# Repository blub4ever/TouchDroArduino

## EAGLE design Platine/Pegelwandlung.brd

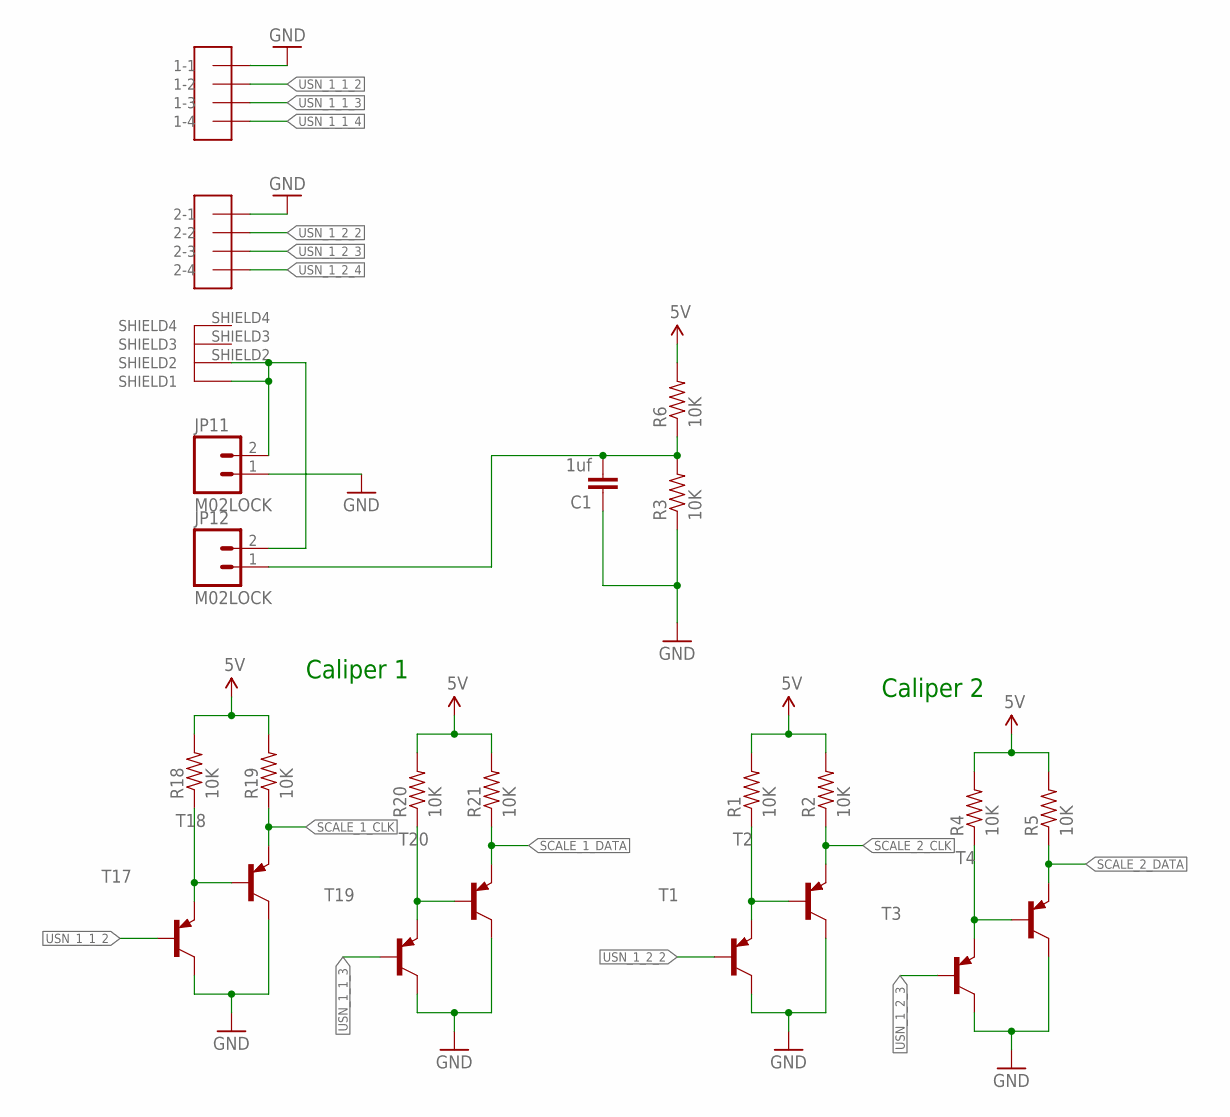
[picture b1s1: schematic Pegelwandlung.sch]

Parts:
C1: 1uf; 0805
JP11, JP12: M02LOCK; 1X02_LOCK
R1, R2, R3, R4, R5, R6, R18, R19, R20, R21: 10K; 0603-RES
T1, T2, T3, T4, T17, T18, T19, T20: -PNP-SOT23-BCE; SOT23-BCE
U$7: USB-A-2

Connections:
1.5V: C1.2, JP12.1, R3.2, R6.1
5V: R1.2, R2.2, R4.2, R5.2, R6.2, R18.2, R19.2, R20.2, R21.2
GND: C1.1, JP11.1, R3.1, T1.C, T2.C, T3.C, T4.C, T17.C, T18.C, T19.C, T20.C, U$7.1-1, U$7.2-1
unnamed: R1.1, T1.E, T2.B
unnamed: JP11.2, JP12.2, U$7.SHIELD1, U$7.SHIELD2
unnamed: R18.1, T17.E, T18.B
unnamed: R4.1, T3.E, T4.B
unnamed: R20.1, T19.E, T20.B
SCALE_1_CLK: R19.1, T18.E
SCALE_1_DATA: R21.1, T20.E
SCALE_2_CLK: R2.1, T2.E
SCALE_2_DATA: R5.1, T4.E
USN_1_1_2: T17.B, U$7.1-2
USN_1_1_3: T19.B, U$7.1-3
USN_1_1_4: U$7.1-4
USN_1_2_2: T1.B, U$7.2-2
USN_1_2_3: T3.B, U$7.2-3
USN_1_2_4: U$7.2-4

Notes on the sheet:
Caliper 2
Caliper 1

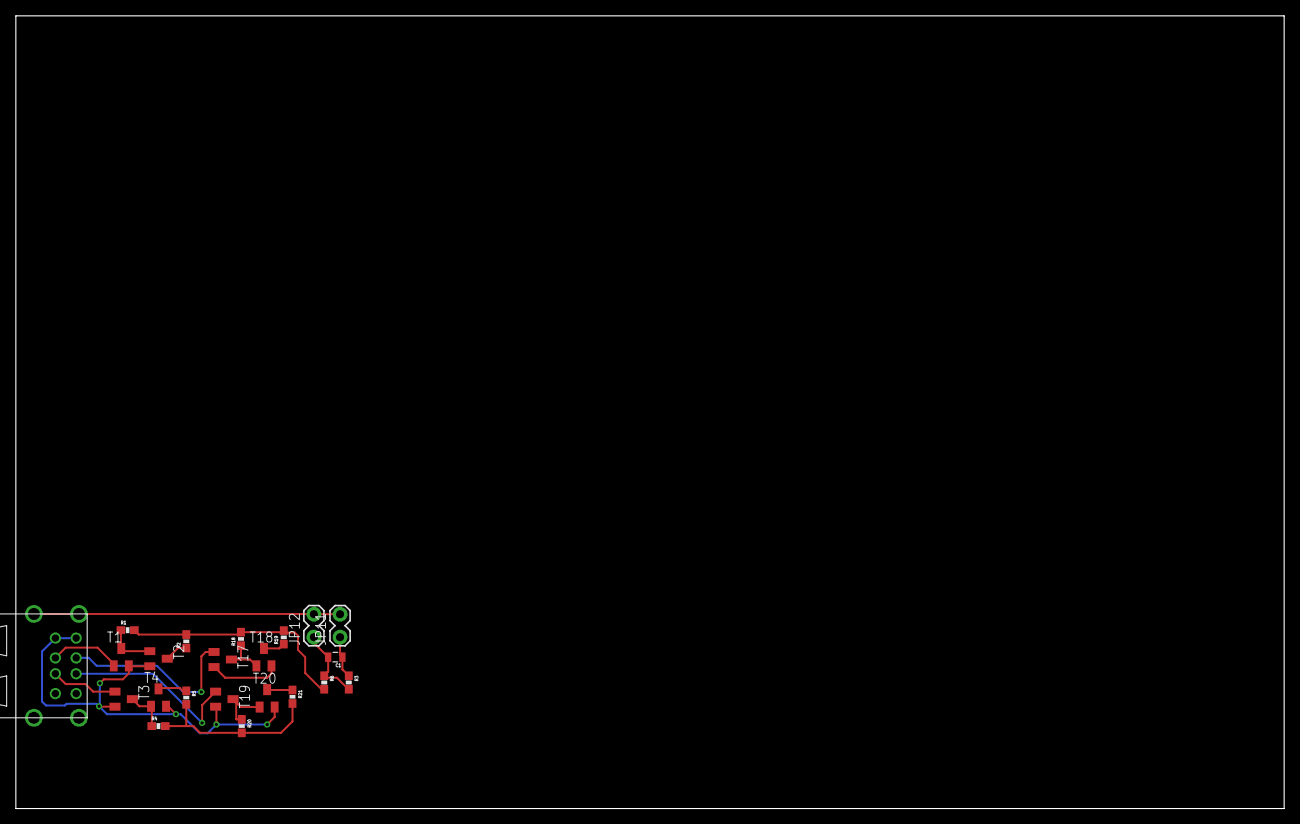
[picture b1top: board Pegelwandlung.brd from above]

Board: 2 copper layers, 160.0 x 100.0 mm, 22 parts (0 on the bottom side), 16 nets.

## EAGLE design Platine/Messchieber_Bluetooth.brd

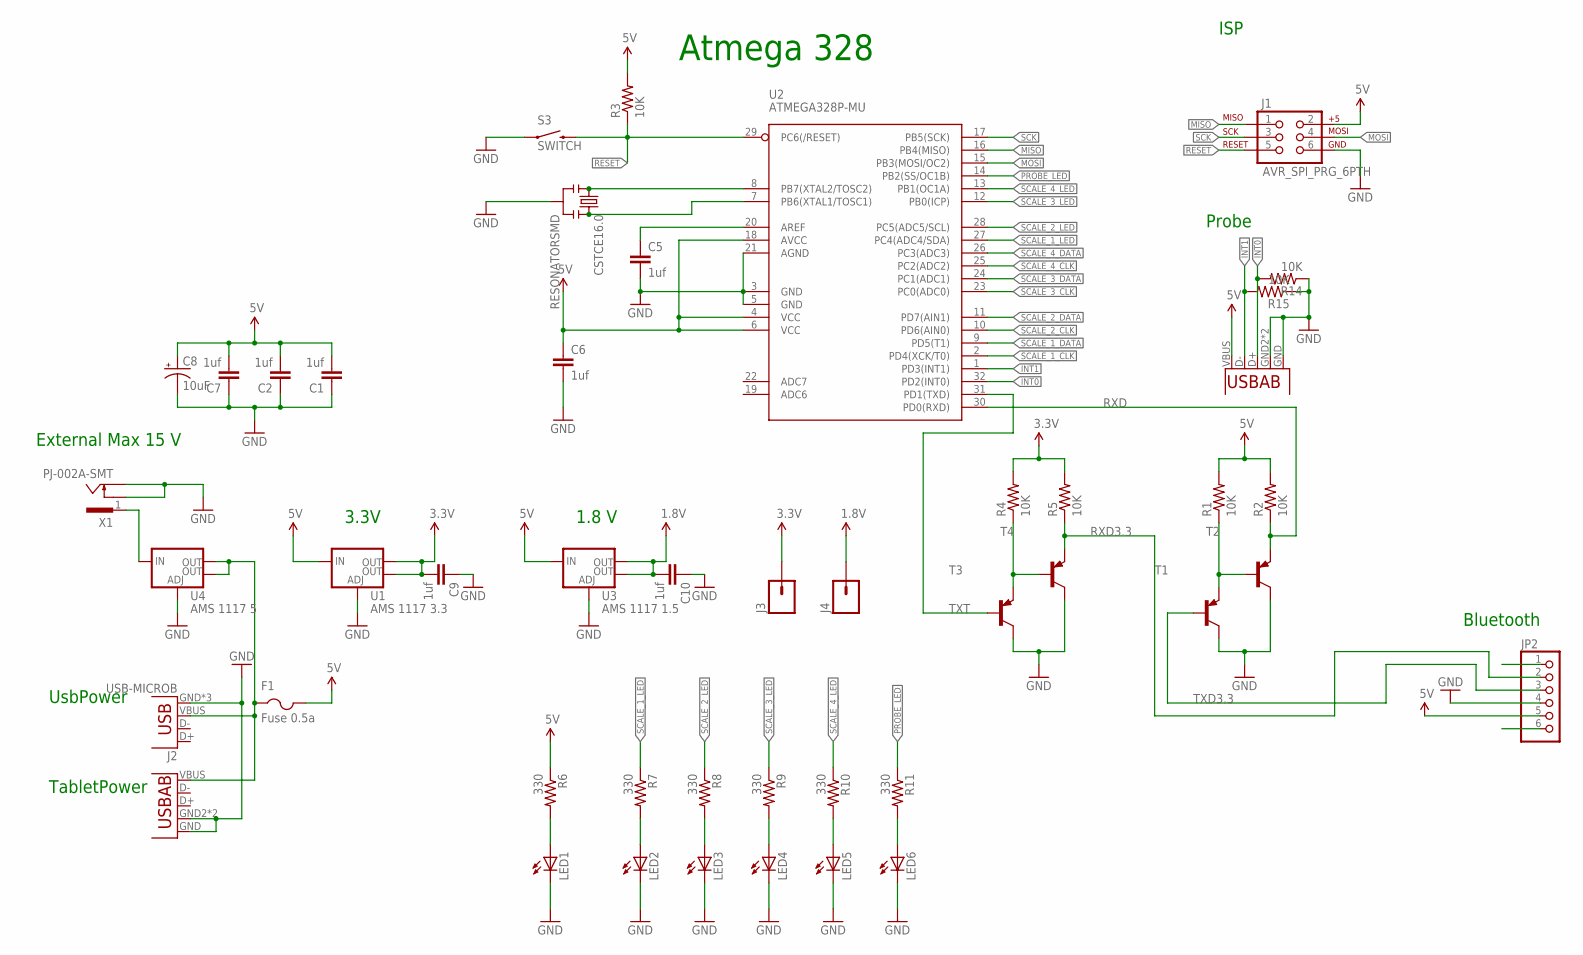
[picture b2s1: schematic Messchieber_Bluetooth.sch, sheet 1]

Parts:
C1, C2, C5, C6, C7, C9, C10: 1uf; 0805
C8: 10uF; EIA3528
CSTCE16.0: RESONATORSMD; RESONATOR-SMD
F1: Fuse 0.5a; 1812
J1: AVR_SPI_PRG_6PTH; 2X3
J2: USB-MICROB
J3, J4: M01PTH; 1X01
JP2: PINHD-1X6; 1X06
LED1, LED2, LED3, LED4, LED5, LED6: LEDSML0805; SML0805
R1, R2, R3, R4, R5, R14, R15: 10K; 0603-RES
R6, R7, R8, R9, R10, R11: 330; 0603
S3: SWITCH; TACTILE-SWITCH-1101NE
T1, T2, T3, T4: -PNP-SOT23-BCE; SOT23-BCE
U1: AMS 1117 3.3; SOT223
U2: ATMEGA328P-MU; TQFP32-08@1
U3: AMS 1117 1.5; SOT223
U4: AMS 1117 5; SOT223
U$1, U$4: USB-A
X1: PJ-002A-SMT; CUI_PJ-002B-SMT

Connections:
1.8V: C10.2, J4.1, U3.2 (OUT), U3.4 (OUT); also elsewhere on the board
3.3V: C9.2, J3.1, R4.2, R5.2, U1.2 (OUT), U1.4 (OUT)
5V: C1.2, C2.2, C6.1, C7.2, C8.A (+), F1.2, J1.2, JP2.5, R1.2, R2.2, R3.2, R6.1, U1.3 (IN), U2.4 (VCC), U2.6 (VCC), U2.18 (AVCC), U3.3 (IN), U$1.VBUS; also elsewhere on the board
GND: C1.1, C2.1, C5.2, C6.2, C7.1, C8.C (-), C9.1, C10.1, CSTCE16.0.2, J1.6, J2.GND, J2.MT1 (GND), J2.MT2 (GND), JP2.4, LED1.C, LED2.C, LED3.C, LED4.C, LED5.C, LED6.C, R14.1, R15.1, S3.P$1 (1), T1.C, T2.C, T3.C, T4.C, U1.1 (ADJ), U2.3 (GND), U2.5 (GND), U2.21 (AGND), U3.1 (ADJ), U4.1 (ADJ), U$1.GND, U$1.GND2 (USBID), U$1.GND3 (USBID), U$4.GND, U$4.GND2 (USBID), U$4.GND3 (USBID), X1.3, X1.4; also elsewhere on the board
INT0: R14.2, U2.32 (PD2(INT0)), U$1.D+
INT1: R15.2, U2.1 (PD3(INT1)), U$1.D-
MISO: J1.1, U2.16 (PB4(MISO))
MOSI: J1.4, U2.15 (PB3(MOSI/OC2))
unnamed: C5.1, U2.20 (AREF)
unnamed: R1.1, T1.E, T2.B
unnamed: R4.1, T3.E, T4.B
unnamed: LED2.A, R7.2
unnamed: CSTCE16.0.1, U2.8 (PB7(XTAL2/TOSC2))
unnamed: F1.1, J2.VBUS, U4.2 (OUT), U4.4 (OUT), U$4.VBUS
unnamed: U4.3 (IN), X1.1
unnamed: LED3.A, R8.2
unnamed: LED1.A, R6.2
unnamed: LED4.A, R9.2
unnamed: LED5.A, R10.2
unnamed: LED6.A, R11.2
unnamed: CSTCE16.0.3, U2.7 (PB6(XTAL1/TOSC1))
PROBE_LED: R11.1, U2.14 (PB2(SS/OC1B))
RESET: J1.5, R3.1, S3.P$2 (2), U2.29 (PC6(/RESET))
RXD: R2.1, T2.E, U2.30 (PD0(RXD))
RXD3.3: JP2.2, R5.1, T4.E
SCALE_1_CLK: U2.2 (PD4(XCK/T0)); also elsewhere on the board
SCALE_1_DATA: U2.9 (PD5(T1)); also elsewhere on the board
SCALE_1_LED: R7.1, U2.27 (PC4(ADC4/SDA))
SCALE_2_CLK: U2.10 (PD6(AIN0)); also elsewhere on the board
SCALE_2_DATA: U2.11 (PD7(AIN1)); also elsewhere on the board
SCALE_2_LED: R8.1, U2.28 (PC5(ADC5/SCL))
SCALE_3_CLK: U2.23 (PC0(ADC0)); also elsewhere on the board
SCALE_3_DATA: U2.24 (PC1(ADC1)); also elsewhere on the board
SCALE_3_LED: R9.1, U2.12 (PB0(ICP))
SCALE_4_CLK: U2.25 (PC2(ADC2)); also elsewhere on the board
SCALE_4_DATA: U2.26 (PC3(ADC3)); also elsewhere on the board
SCALE_4_LED: R10.1, U2.13 (PB1(OC1A))
SCK: J1.3, U2.17 (PB5(SCK))
TXD3.3: JP2.3, T1.B
TXT: T3.B, U2.31 (PD1(TXD))

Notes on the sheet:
Atmega 328
Bluetooth
Probe
ISP
UsbPower
TabletPower
External Max 15 V
3.3V
1.8 V

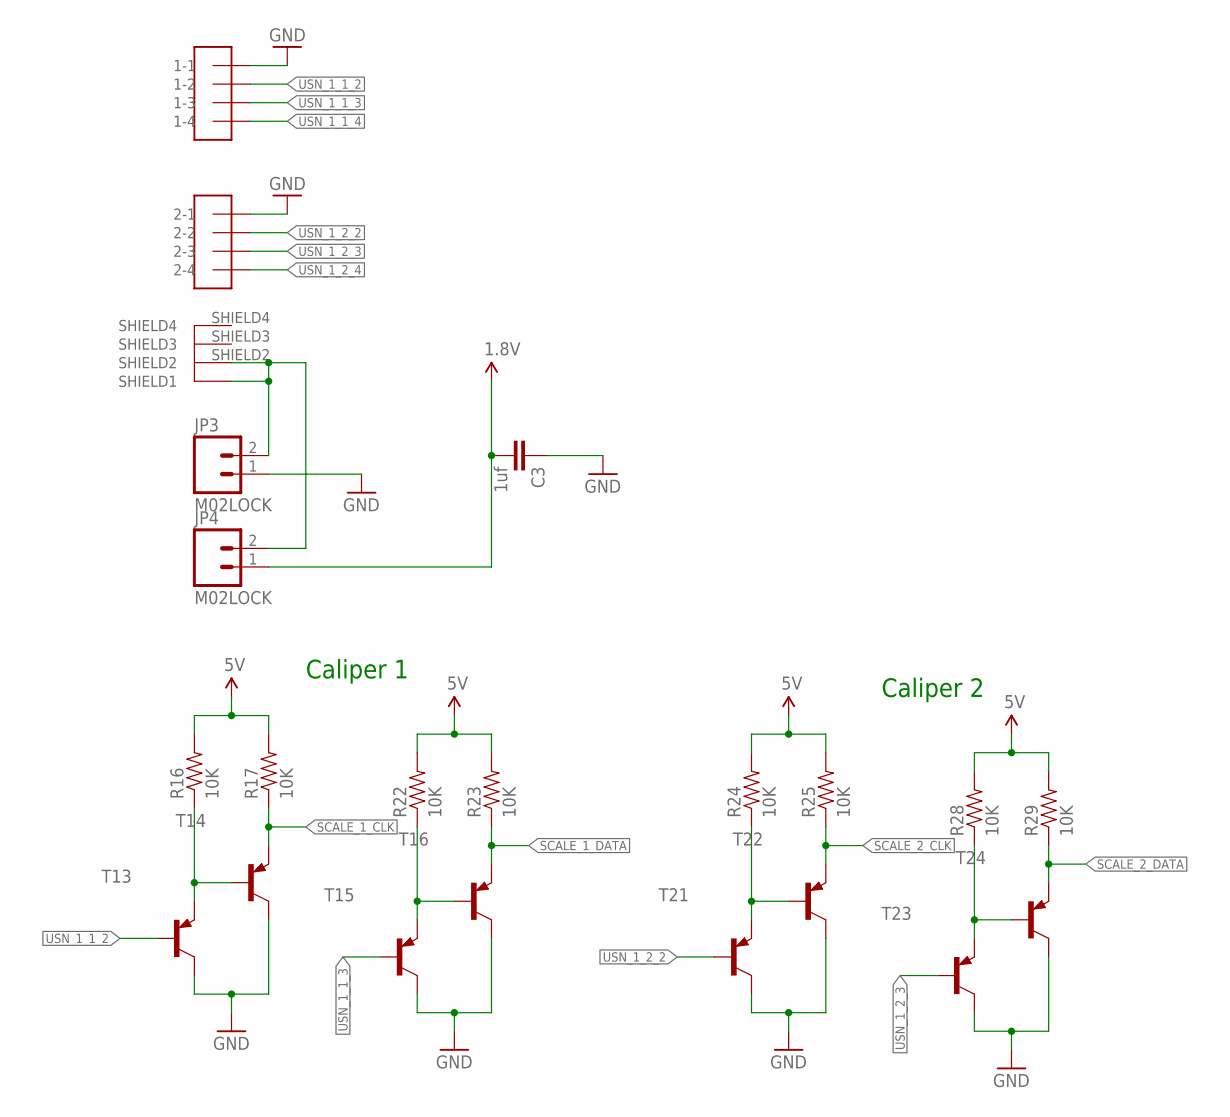
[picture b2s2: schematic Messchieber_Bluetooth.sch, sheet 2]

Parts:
C3: 1uf; 0805
JP3, JP4: M02LOCK; 1X02_LOCK
R16, R17, R22, R23, R24, R25, R28, R29: 10K; 0603-RES
T13, T14, T15, T16, T21, T22, T23, T24: -PNP-SOT23-BCE; SOT23-BCE
U$2: USB-A-2

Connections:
1.8V: C3.2, JP4.1; also elsewhere on the board
5V: R16.2, R17.2, R22.2, R23.2, R24.2, R25.2, R28.2, R29.2; also elsewhere on the board
GND: C3.1, JP3.1, T13.C, T14.C, T15.C, T16.C, T21.C, T22.C, T23.C, T24.C, U$2.1-1, U$2.2-1; also elsewhere on the board
unnamed: JP3.2, JP4.2, U$2.SHIELD1, U$2.SHIELD2
unnamed: R16.1, T13.E, T14.B
unnamed: R22.1, T15.E, T16.B
unnamed: R24.1, T21.E, T22.B
unnamed: R28.1, T23.E, T24.B
SCALE_1_CLK: R17.1, T14.E; also elsewhere on the board
SCALE_1_DATA: R23.1, T16.E; also elsewhere on the board
SCALE_2_CLK: R25.1, T22.E; also elsewhere on the board
SCALE_2_DATA: R29.1, T24.E; also elsewhere on the board
USN_1_1_2: T13.B, U$2.1-2
USN_1_1_3: T15.B, U$2.1-3
USN_1_1_4: U$2.1-4
USN_1_2_2: T21.B, U$2.2-2
USN_1_2_3: T23.B, U$2.2-3
USN_1_2_4: U$2.2-4

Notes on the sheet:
Caliper 2
Caliper 1

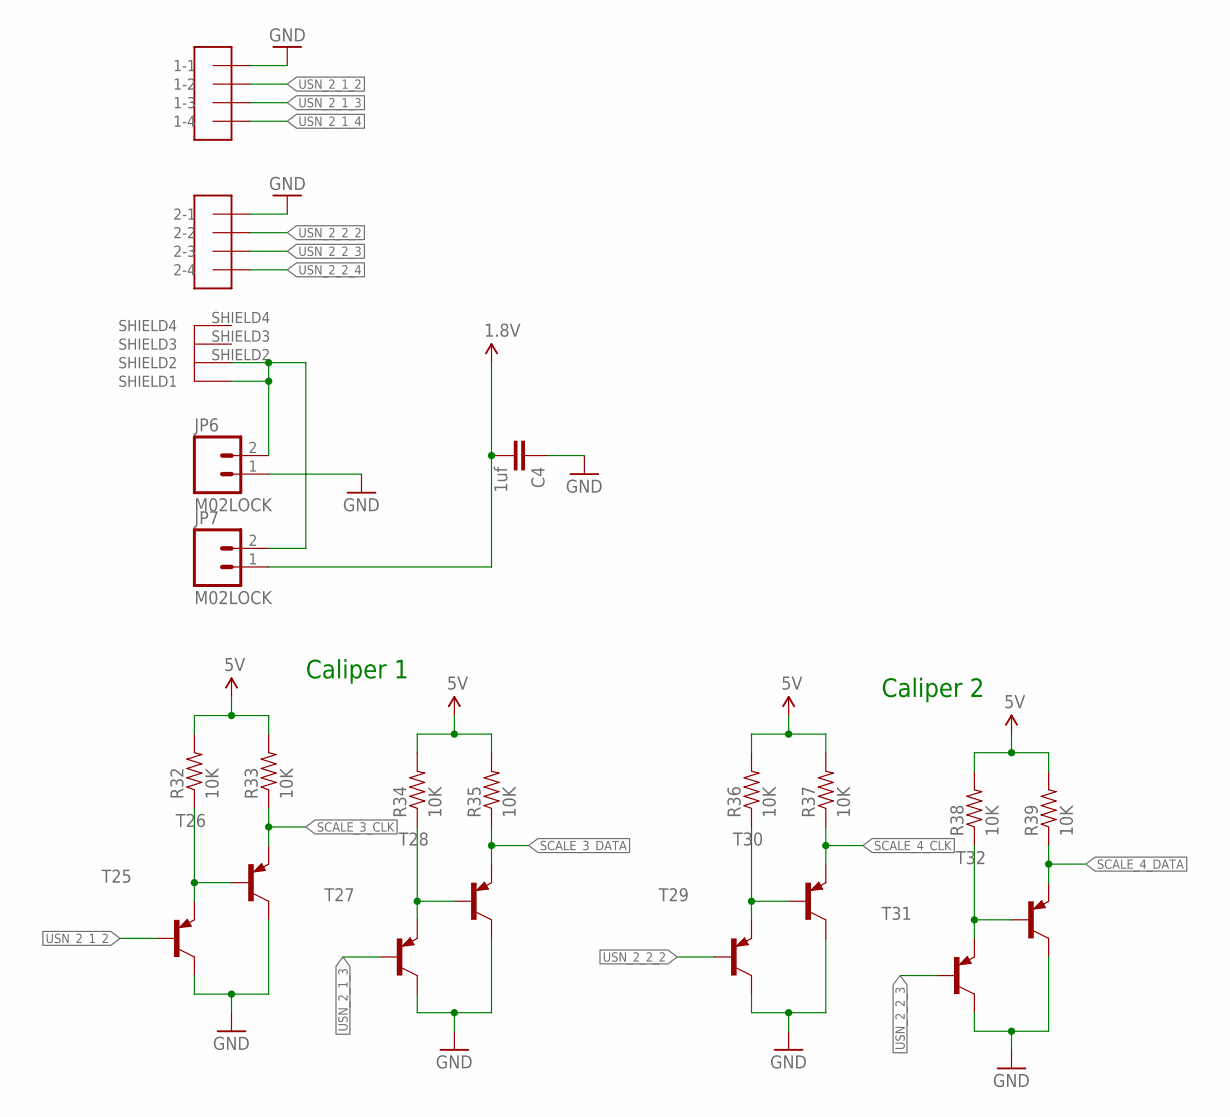
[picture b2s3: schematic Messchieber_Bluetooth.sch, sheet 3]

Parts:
C4: 1uf; 0805
JP6, JP7: M02LOCK; 1X02_LOCK
R32, R33, R34, R35, R36, R37, R38, R39: 10K; 0603-RES
T25, T26, T27, T28, T29, T30, T31, T32: -PNP-SOT23-BCE; SOT23-BCE
U$3: USB-A-2

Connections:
1.8V: C4.2, JP7.1; also elsewhere on the board
5V: R32.2, R33.2, R34.2, R35.2, R36.2, R37.2, R38.2, R39.2; also elsewhere on the board
GND: C4.1, JP6.1, T25.C, T26.C, T27.C, T28.C, T29.C, T30.C, T31.C, T32.C, U$3.1-1, U$3.2-1; also elsewhere on the board
unnamed: JP6.2, JP7.2, U$3.SHIELD1, U$3.SHIELD2
unnamed: R32.1, T25.E, T26.B
unnamed: R34.1, T27.E, T28.B
unnamed: R36.1, T29.E, T30.B
unnamed: R38.1, T31.E, T32.B
SCALE_3_CLK: R33.1, T26.E; also elsewhere on the board
SCALE_3_DATA: R35.1, T28.E; also elsewhere on the board
SCALE_4_CLK: R37.1, T30.E; also elsewhere on the board
SCALE_4_DATA: R39.1, T32.E; also elsewhere on the board
USN_2_1_2: T25.B, U$3.1-2
USN_2_1_3: T27.B, U$3.1-3
USN_2_1_4: U$3.1-4
USN_2_2_2: T29.B, U$3.2-2
USN_2_2_3: T31.B, U$3.2-3
USN_2_2_4: U$3.2-4

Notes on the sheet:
Caliper 2
Caliper 1

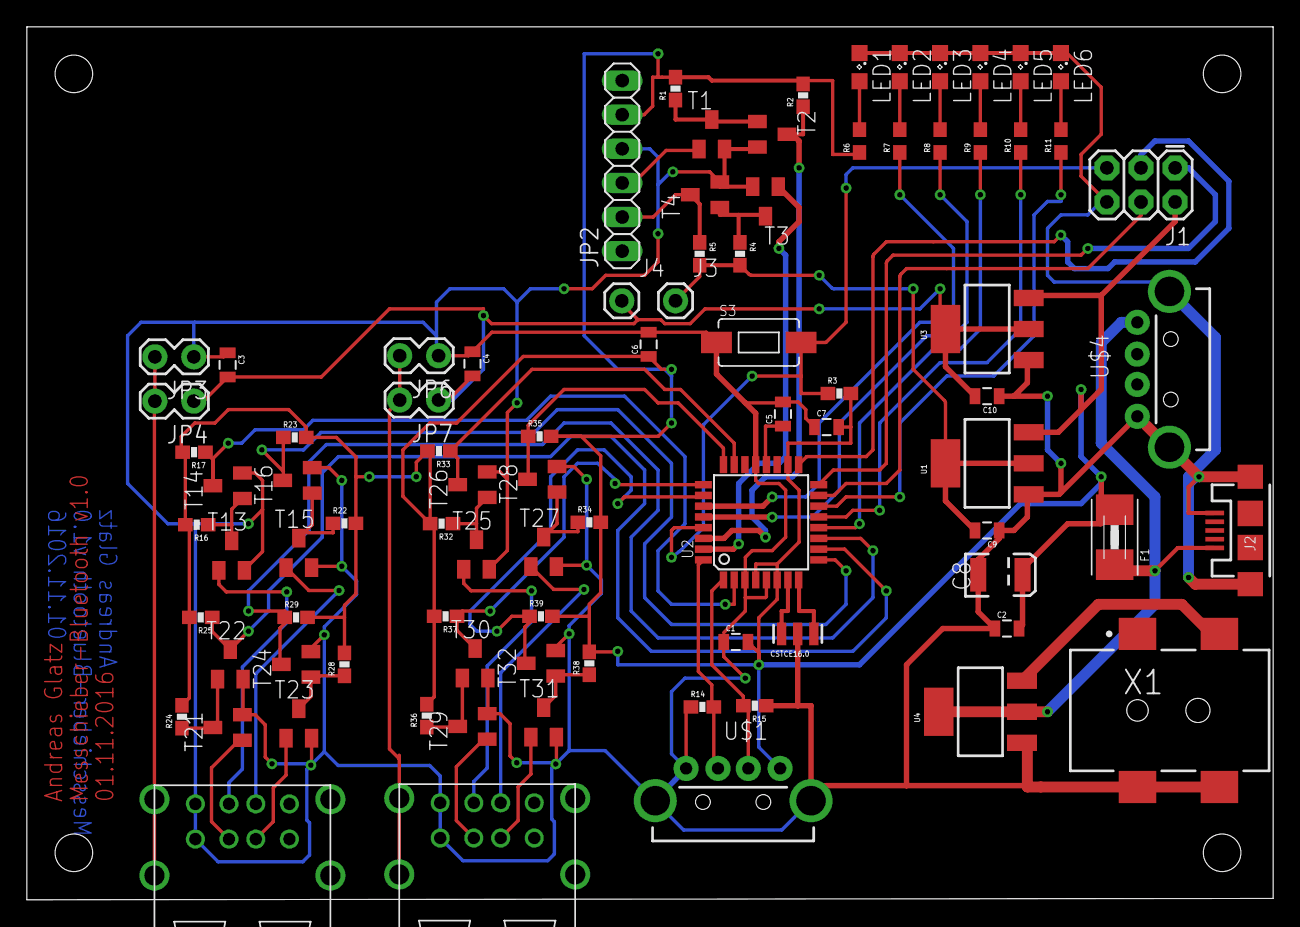
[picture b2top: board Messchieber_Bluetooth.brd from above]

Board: 2 copper layers, 92.8 x 65.0 mm, 86 parts (0 on the bottom side), 58 nets.

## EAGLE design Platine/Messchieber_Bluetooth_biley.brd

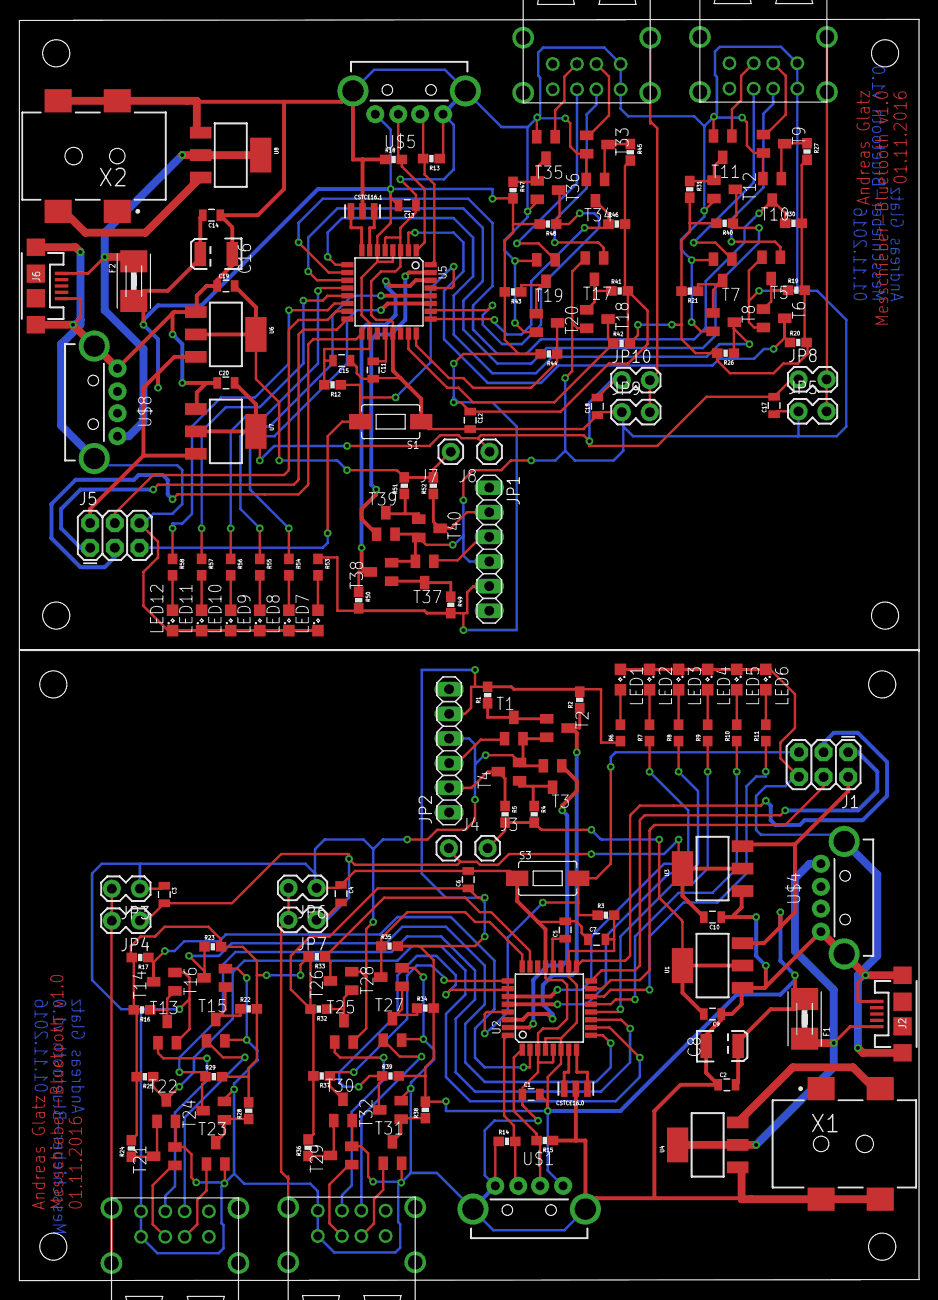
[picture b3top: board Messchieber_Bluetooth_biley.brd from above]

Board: 2 copper layers, 92.8 x 130.1 mm, 172 parts (0 on the bottom side), 116 nets.

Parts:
C1, C2, C3, C4, C5, C6, C7, C9, C10, C11, C12, C13, C14, C15, C17, C18, C19, C20: 1uf; 0805
C8, C16: 10uF; EIA3528
CSTCE16.0, CSTCE16.1: RESONATORSMD; RESONATOR-SMD
F1, F2: Fuse 0.5a; 1812
J1, J5: AVR_SPI_PRG_6PTH; 2X3
J2, J6: USB-MICROB
J3, J4, J7, J8: 1X01
JP1, JP2: 1X06
JP3, JP4, JP5, JP6, JP7, JP8, JP9, JP10: M02LOCK; 1X02_LOCK
LED1, LED2, LED3, LED4, LED5, LED6, LED7, LED8, LED9, LED10, LED11, LED12: SML0805
R1, R2, R3, R4, R5, R12, R13, R14, R15, R16, R17, R18, R19, R20, R21, R22, R23, R24, R25, R26, R27, R28, R29, R30, R31, R32, R33, R34, R35, R36, R37, R38, R39, R40, R41, R42, R43, R44, R45, R46, R47, R48, R49, R50, R51, R52: 10K; 0603-RES
R6, R7, R8, R9, R10, R11, R53, R54, R55, R56, R57, R58: 330; 0603
S1, S3: SWITCH; TACTILE-SWITCH-1101NE
T1, T2, T3, T4, T5, T6, T7, T8, T9, T10, T11, T12, T13, T14, T15, T16, T17, T18, T19, T20, T21, T22, T23, T24, T25, T26, T27, T28, T29, T30, T31, T32, T33, T34, T35, T36, T37, T38, T39, T40: SOT23-BCE
U1, U6: AMS 1117 3.3; SOT223
U2, U5: ATMEGA328P-MU; TQFP32-08@1
U3, U7: AMS 1117 1.5; SOT223
U4, U8: AMS 1117 5; SOT223
U$1, U$4, U$5, U$8: USB-A
U$2, U$3, U$6, U$7: USB-A-2
X1, X2: PJ-002A-SMT; CUI_PJ-002B-SMT

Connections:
1.8V: C3.2, C4.2, C10.2, J4.1, JP4.1, JP7.1, U3.2, U3.4
1.8V1: C17.2, C18.2, C20.2, J8.1, JP8.1, JP10.1, U7.2, U7.4
3.3V: C9.2, J3.1, R4.2, R5.2, U1.2, U1.4
3.3V1: C19.2, J7.1, R51.2, R52.2, U6.2, U6.4
5V: C1.2, C2.2, C6.1, C7.2, C8.A, F1.2, J1.2, JP2.5, R1.2, R2.2, R3.2, R6.1, R16.2, R17.2, R22.2, R23.2, R24.2, R25.2, R28.2, R29.2, R32.2, R33.2, R34.2, R35.2, R36.2, R37.2, R38.2, R39.2, U1.3, U2.4, U2.6, U2.18, U3.3, U$1.VBUS
5V1: C12.1, C13.2, C14.2, C15.2, C16.A, F2.2, J5.2, JP1.5, R12.2, R19.2, R20.2, R21.2, R26.2, R27.2, R30.2, R31.2, R40.2, R41.2, R42.2, R43.2, R44.2, R45.2, R46.2, R47.2, R48.2, R49.2, R50.2, R53.1, U5.4, U5.6, U5.18, U6.3, U7.3, U$5.VBUS
GND: C1.1, C2.1, C3.1, C4.1, C5.2, C6.2, C7.1, C8.C, C9.1, C10.1, CSTCE16.0.2, J1.6, J2.GND, J2.MT1, J2.MT2, JP2.4, JP3.1, JP6.1, LED1.C, LED2.C, LED3.C, LED4.C, LED5.C, LED6.C, R14.1, R15.1, S3.P$1, T1.C, T2.C, T3.C, T4.C, T13.C, T14.C, T15.C, T16.C, T21.C, T22.C, T23.C, T24.C, T25.C, T26.C, T27.C, T28.C, T29.C, T30.C, T31.C, T32.C, U1.1, U2.3, U2.5, U2.21, U3.1, U4.1, U$1.GND, U$1.GND2, U$1.GND3, U$2.1-1, U$2.2-1, U$3.1-1, U$3.2-1, U$4.GND, U$4.GND2, U$4.GND3, X1.3, X1.4
GND1: C11.2, C12.2, C13.1, C14.1, C15.1, C16.C, C17.1, C18.1, C19.1, C20.1, CSTCE16.1.2, J5.6, J6.GND, J6.MT1, J6.MT2, JP1.4, JP5.1, JP9.1, LED7.C, LED8.C, LED9.C, LED10.C, LED11.C, LED12.C, R13.1, R18.1, S1.P$1, T5.C, T6.C, T7.C, T8.C, T9.C, T10.C, T11.C, T12.C, T17.C, T18.C, T19.C, T20.C, T33.C, T34.C, T35.C, T36.C, T37.C, T38.C, T39.C, T40.C, U5.3, U5.5, U5.21, U6.1, U7.1, U8.1, U$5.GND, U$5.GND2, U$5.GND3, U$6.1-1, U$6.2-1, U$7.1-1, U$7.2-1, U$8.GND, U$8.GND2, U$8.GND3, X2.3, X2.4
INT0: R14.2, U2.32, U$1.D+
INT1: R15.2, U2.1, U$1.D-
INT2: R13.2, U5.32, U$5.D+
INT3: R18.2, U5.1, U$5.D-
MISO: J1.1, U2.16
MISO1: J5.1, U5.16
MOSI: J1.4, U2.15
MOSI1: J5.4, U5.15
unnamed: C5.1, U2.20
unnamed: R1.1, T1.E, T2.B
unnamed: JP3.2, JP4.2, U$2.SHIELD1, U$2.SHIELD2
unnamed: R4.1, T3.E, T4.B
unnamed: LED2.A, R7.2
unnamed: CSTCE16.0.1, U2.8
unnamed: F1.1, J2.VBUS, U4.2, U4.4, U$4.VBUS
unnamed: U4.3, X1.1
unnamed: LED3.A, R8.2
unnamed: LED1.A, R6.2
unnamed: R16.1, T13.E, T14.B
unnamed: LED4.A, R9.2
unnamed: LED5.A, R10.2
unnamed: R22.1, T15.E, T16.B
unnamed: R24.1, T21.E, T22.B
unnamed: LED6.A, R11.2
unnamed: R28.1, T23.E, T24.B
unnamed: CSTCE16.0.3, U2.7
unnamed: JP6.2, JP7.2, U$3.SHIELD1, U$3.SHIELD2
unnamed: R32.1, T25.E, T26.B
unnamed: R34.1, T27.E, T28.B
unnamed: CSTCE16.1.3, U5.7
unnamed: CSTCE16.1.1, U5.8
unnamed: R36.1, T29.E, T30.B
unnamed: R38.1, T31.E, T32.B
unnamed: C11.1, U5.20
unnamed: JP5.2, JP8.2, U$6.SHIELD1, U$6.SHIELD2
unnamed: R19.1, T5.E, T6.B
unnamed: R21.1, T7.E, T8.B
unnamed: R27.1, T9.E, T10.B
unnamed: R31.1, T11.E, T12.B
unnamed: JP9.2, JP10.2, U$7.SHIELD1, U$7.SHIELD2
unnamed: R41.1, T17.E, T18.B
unnamed: R43.1, T19.E, T20.B
unnamed: R45.1, T33.E, T34.B
unnamed: R47.1, T35.E, T36.B
unnamed: R49.1, T37.E, T38.B
unnamed: R51.1, T39.E, T40.B
unnamed: F2.1, J6.VBUS, U8.2, U8.4, U$8.VBUS
unnamed: LED7.A, R53.2
unnamed: U8.3, X2.1
unnamed: LED8.A, R54.2
unnamed: LED9.A, R55.2
unnamed: LED10.A, R56.2
unnamed: LED11.A, R57.2
unnamed: LED12.A, R58.2
PROBE_LED: R11.1, U2.14
PROBE_LED1: R58.1, U5.14
RESET: J1.5, R3.1, S3.P$2, U2.29
RESET1: J5.5, R12.1, S1.P$2, U5.29
RXD: R2.1, T2.E, U2.30
RXD1: R50.1, T38.E, U5.30
RXD3.1: JP1.2, R52.1, T40.E
RXD3.3: JP2.2, R5.1, T4.E
SCALE_1_CLK: R17.1, T14.E, U2.2
SCALE_1_CLK1: R20.1, T6.E, U5.2
SCALE_1_DATA: R23.1, T16.E, U2.9
SCALE_1_DATA1: R26.1, T8.E, U5.9
SCALE_1_LED: R7.1, U2.27
SCALE_1_LED1: R54.1, U5.27
SCALE_2_CLK: R25.1, T22.E, U2.10
SCALE_2_CLK1: R30.1, T10.E, U5.10
SCALE_2_DATA: R29.1, T24.E, U2.11
SCALE_2_DATA1: R40.1, T12.E, U5.11
SCALE_2_LED: R8.1, U2.28
SCALE_2_LED1: R55.1, U5.28
SCALE_3_CLK: R33.1, T26.E, U2.23
SCALE_3_CLK1: R42.1, T18.E, U5.23
SCALE_3_DATA: R35.1, T28.E, U2.24
SCALE_3_DATA1: R44.1, T20.E, U5.24
SCALE_3_LED: R9.1, U2.12
SCALE_3_LED1: R56.1, U5.12
SCALE_4_CLK: R37.1, T30.E, U2.25
SCALE_4_CLK1: R46.1, T34.E, U5.25
SCALE_4_DATA: R39.1, T32.E, U2.26
SCALE_4_DATA1: R48.1, T36.E, U5.26
SCALE_4_LED: R10.1, U2.13
SCALE_4_LED1: R57.1, U5.13
SCK: J1.3, U2.17
SCK1: J5.3, U5.17
TXD3.1: JP1.3, T37.B
TXD3.3: JP2.3, T1.B
TXT: T3.B, U2.31
TXT1: T39.B, U5.31
USN_1_1_2: T13.B, U$2.1-2
USN_1_1_3: T15.B, U$2.1-3
USN_1_1_5: T7.B, U$6.1-3
USN_1_1_6: T5.B, U$6.1-2
USN_1_2_2: T21.B, U$2.2-2
USN_1_2_3: T23.B, U$2.2-3
USN_1_2_5: T11.B, U$6.2-3
USN_1_2_6: T9.B, U$6.2-2
USN_2_1_1: T17.B, U$7.1-2
USN_2_1_2: T25.B, U$3.1-2
USN_2_1_3: T27.B, U$3.1-3
USN_2_1_5: T19.B, U$7.1-3
USN_2_2_1: T33.B, U$7.2-2
USN_2_2_2: T29.B, U$3.2-2
USN_2_2_3: T31.B, U$3.2-3
USN_2_2_5: T35.B, U$7.2-3

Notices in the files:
parts and their libraries:
SparkFun-Resistors: Licensing: Creative Commons ShareAlike 4.0 International - https://creativecommons.org/licenses/by-sa/4.0
